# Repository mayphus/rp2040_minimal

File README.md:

> **Archived after consolidation — 18 September 2026.** Maintenance and original Git history now live in [hardware-designs](https://github.com/mayphus/hardware-designs/tree/main/boards/rp2040_minimal). This repository is retained as a historical reference; use the successor for new work.

---

# Minimal RP2040 Board

> **Status:** Hardware snapshot — preserved for reference and not actively maintained.

RP2040 minimal design with USB C

from RP2040 offical example.

[Minimal KiCAD](https://datasheets.raspberrypi.com/rp2040/Minimal-KiCAD.zip)
[Hardware design with rp2040](https://datasheets.raspberrypi.com/rp2040/hardware-design-with-rp2040.pdf)

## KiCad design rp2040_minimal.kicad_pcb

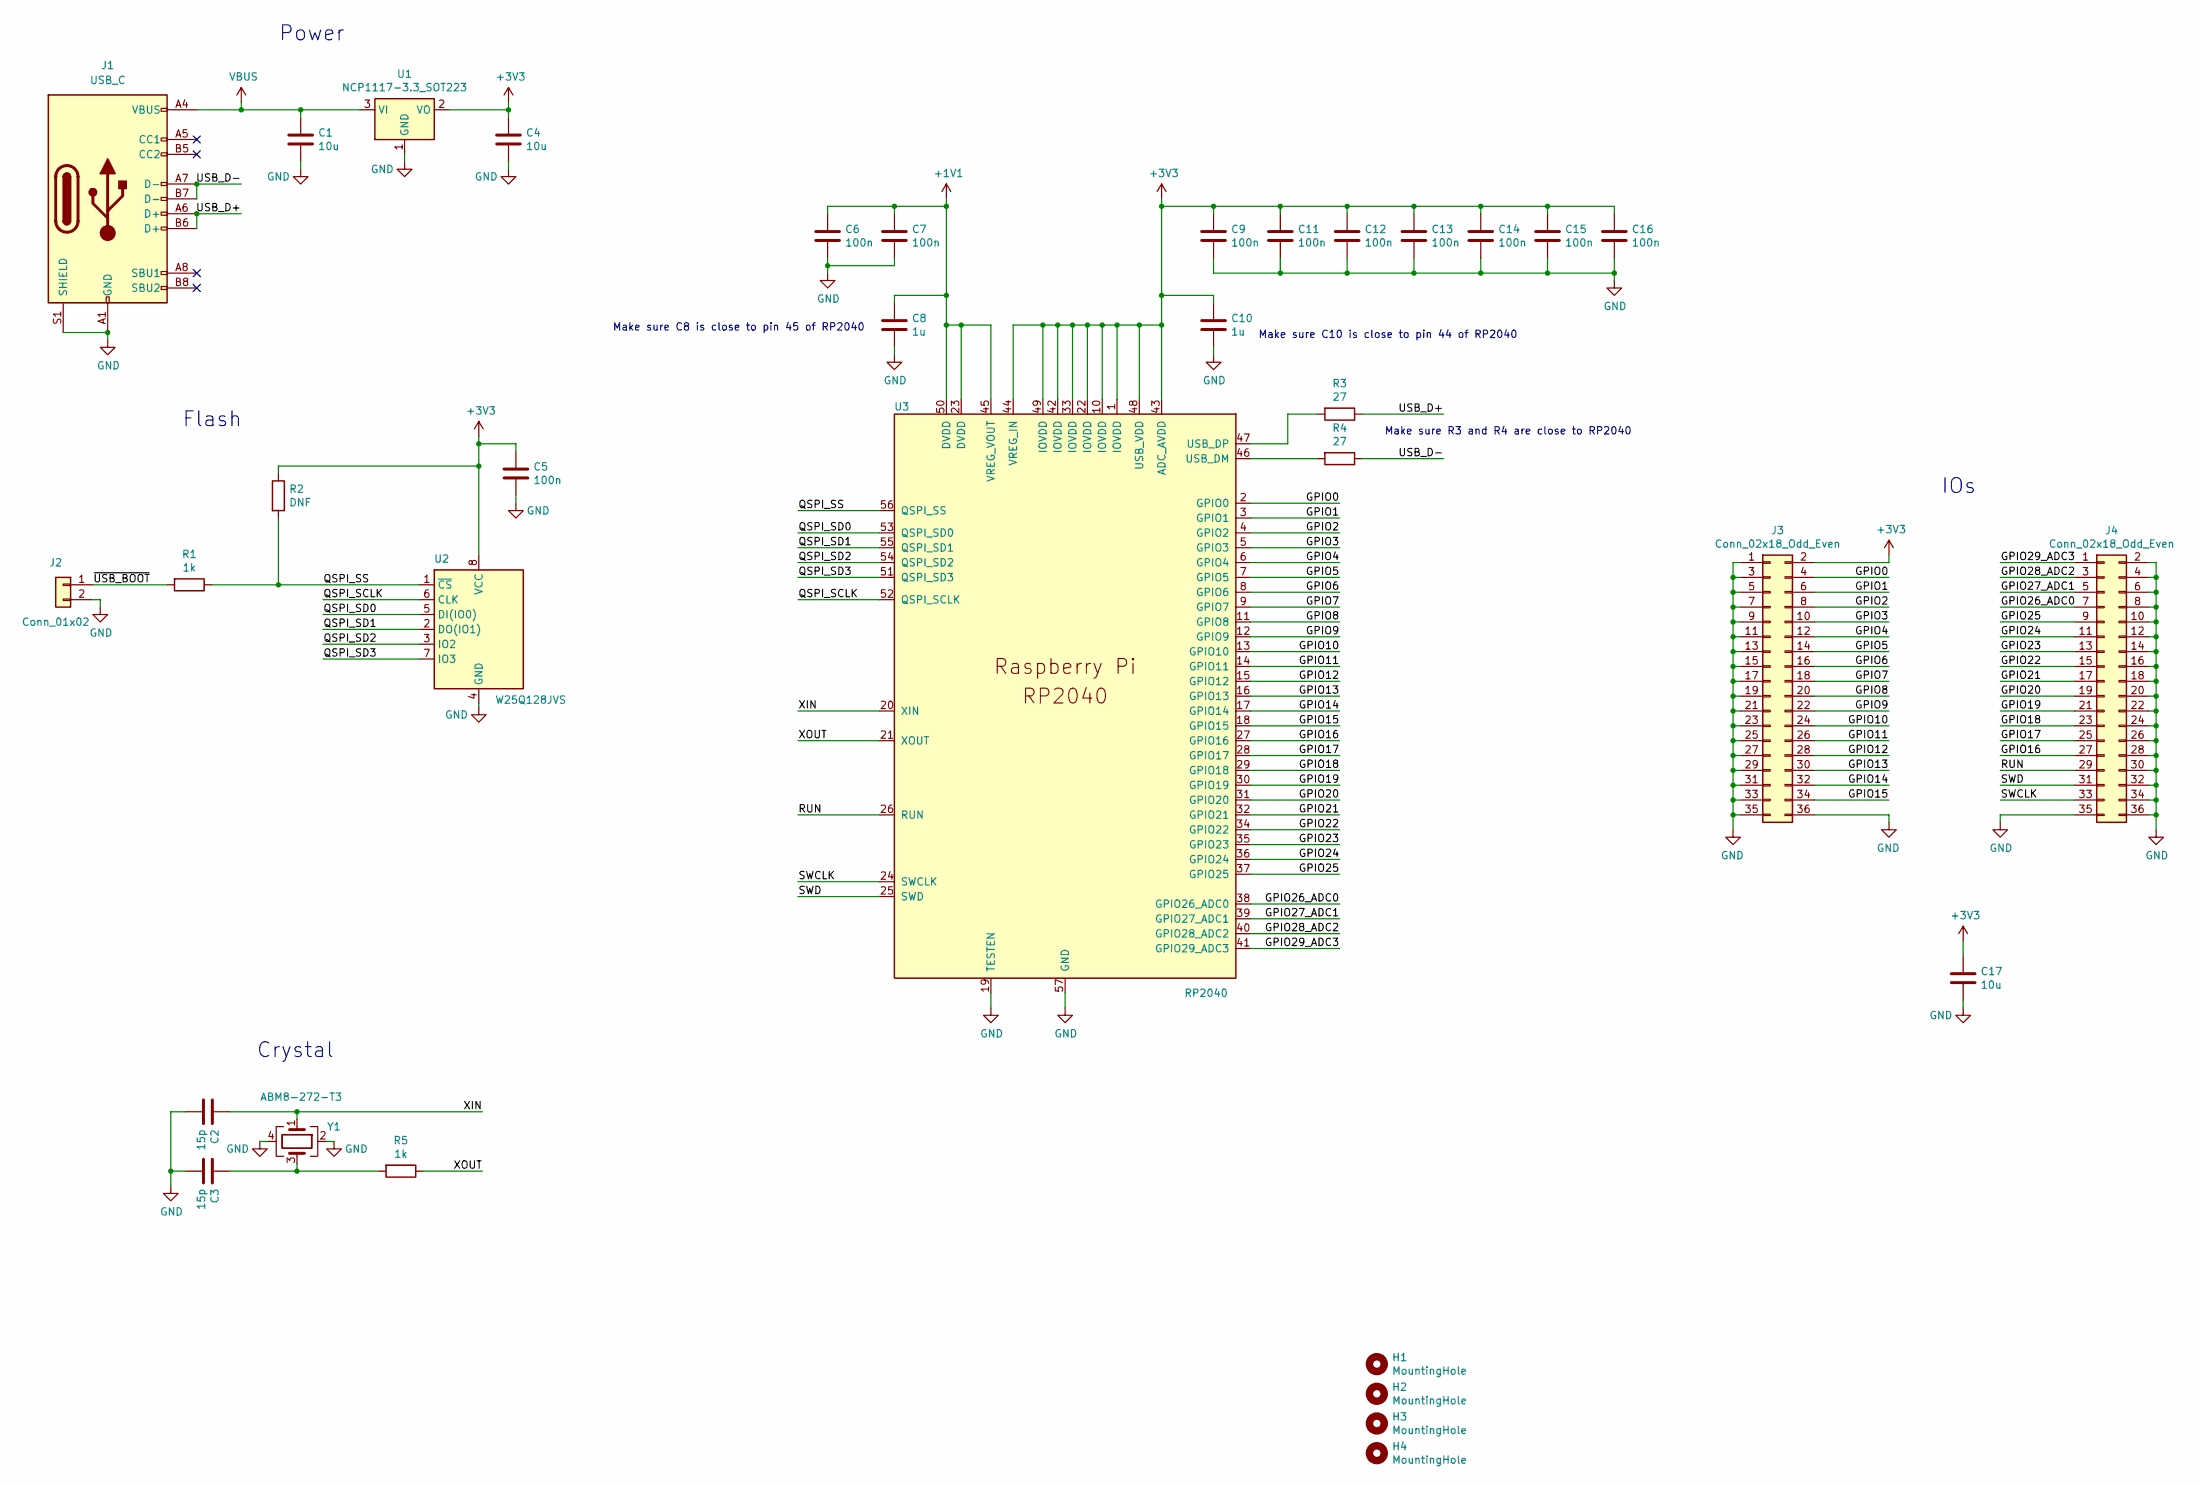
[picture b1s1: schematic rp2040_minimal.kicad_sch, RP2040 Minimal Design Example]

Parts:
C1, C4, C17: 10u; C_0805_2012Metric
C2, C3: 15p; C_0402_1005Metric
C5, C6, C7, C9, C11, C12, C13, C14, C15, C16: 100n; C_0402_1005Metric
C8, C10: 1u; C_0402_1005Metric
H1, H2, H3, H4: MountingHole; MountingHole_2.7mm_M2.5
J1: USB_C; USB_C_Receptacle_GCT_USB4105-xx-A_16P_TopMnt_Horizontal
J2: Conn_01x02; PinHeader_1x02_P2.54mm_Vertical
J3, J4: Conn_02x18_Odd_Even; PinHeader_2x18_P2.54mm_Vertical
R1, R5: 1k; R_0402_1005Metric
R2: DNF; R_0402_1005Metric
R3, R4: 27; R_0402_1005Metric
U1: NCP1117-3.3_SOT223; SOT-223-3_TabPin2
U2: W25Q128JVS; SOIC-8_5.23x5.23mm_P1.27mm
U3: RP2040; RP2040-QFN-56
Y1: ABM8-272-T3; Crystal_SMD_3225-4Pin_3.2x2.5mm

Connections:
+1V1: C6.1, C7.1, C8.1, U3.23 (DVDD), U3.45 (VREG_VOUT), U3.50 (DVDD)
+3V3: C4.1, C5.1, C9.1, C10.1, C11.1, C12.1, C13.1, C14.1, C15.1, C16.1, C17.1, J3.2, R2.1, U1.2 (VO), U2.8 (VCC), U3.1 (IOVDD), U3.10 (IOVDD), U3.22 (IOVDD), U3.33 (IOVDD), U3.42 (IOVDD), U3.43 (ADC_AVDD), U3.44 (VREG_IN), U3.48 (USB_VDD), U3.49 (IOVDD)
/GPIO0: J3.4, U3.2 (GPIO0)
/GPIO1: J3.6, U3.3 (GPIO1)
/GPIO2: J3.8, U3.4 (GPIO2)
/GPIO3: J3.10, U3.5 (GPIO3)
/GPIO4: J3.12, U3.6 (GPIO4)
/GPIO5: J3.14, U3.7 (GPIO5)
/GPIO6: J3.16, U3.8 (GPIO6)
/GPIO7: J3.18, U3.9 (GPIO7)
/GPIO8: J3.20, U3.11 (GPIO8)
/GPIO9: J3.22, U3.12 (GPIO9)
/GPIO10: J3.24, U3.13 (GPIO10)
/GPIO11: J3.26, U3.14 (GPIO11)
/GPIO12: J3.28, U3.15 (GPIO12)
/GPIO13: J3.30, U3.16 (GPIO13)
/GPIO14: J3.32, U3.17 (GPIO14)
/GPIO15: J3.34, U3.18 (GPIO15)
/GPIO16: J4.27, U3.27 (GPIO16)
/GPIO17: J4.25, U3.28 (GPIO17)
/GPIO18: J4.23, U3.29 (GPIO18)
/GPIO19: J4.21, U3.30 (GPIO19)
/GPIO20: J4.19, U3.31 (GPIO20)
/GPIO21: J4.17, U3.32 (GPIO21)
/GPIO22: J4.15, U3.34 (GPIO22)
/GPIO23: J4.13, U3.35 (GPIO23)
/GPIO24: J4.11, U3.36 (GPIO24)
/GPIO25: J4.9, U3.37 (GPIO25)
/GPIO26_ADC0: J4.7, U3.38 (GPIO26_ADC0)
/GPIO27_ADC1: J4.5, U3.39 (GPIO27_ADC1)
/GPIO28_ADC2: J4.3, U3.40 (GPIO28_ADC2)
/GPIO29_ADC3: J4.1, U3.41 (GPIO29_ADC3)
/QSPI_SCLK: U2.6 (CLK), U3.52 (QSPI_SCLK)
/QSPI_SD0: U2.5 (DI(IO0)), U3.53 (QSPI_SD0)
/QSPI_SD1: U2.2 (DO(IO1)), U3.55 (QSPI_SD1)
/QSPI_SD2: U2.3 (IO2), U3.54 (QSPI_SD2)
/QSPI_SD3: U2.7 (IO3), U3.51 (QSPI_SD3)
/QSPI_SS: R1.1, R2.2, U2.1 (~CS), U3.56 (QSPI_SS)
/RUN: J4.29, U3.26 (RUN)
/SWCLK: J4.33, U3.24 (SWCLK)
/SWD: J4.31, U3.25 (SWD)
/USB_D+: J1.A6 (D+), J1.B6 (D+), R3.1
/USB_D-: J1.A7 (D-), J1.B7 (D-), R4.1
/XIN: C2.1, U3.20 (XIN), Y1.1
/XOUT: R5.1, U3.21 (XOUT)
/~USB_BOOT: J2.1, R1.2
GND: C1.2, C2.2, C3.2, C4.2, C5.2, C6.2, C7.2, C8.2, C9.2, C10.2, C11.2, C12.2, C13.2, C14.2, C15.2, C16.2, C17.2, J1.A1 (GND), J1.A12 (GND), J1.B1 (GND), J1.B12 (GND), J1.S1 (SHIELD), J2.2, J3.1, J3.3, J3.5, J3.7, J3.9, J3.11, J3.13, J3.15, J3.17, J3.19, J3.21, J3.23, J3.25, J3.27, J3.29, J3.31, J3.33, J3.35, J3.36, J4.2, J4.4, J4.6, J4.8, J4.10, J4.12, J4.14, J4.16, J4.18, J4.20, J4.22, J4.24, J4.26, J4.28, J4.30, J4.32, J4.34, J4.35, J4.36, U1.1 (GND), U2.4 (GND), U3.19 (TESTEN), U3.57 (GND), Y1.2, Y1.4
unnamed: C3.1, R5.2, Y1.3
unnamed: R4.2, U3.46 (USB_DM)
unnamed: R3.2, U3.47 (USB_DP)
VBUS: C1.1, J1.A4 (VBUS), J1.A9 (VBUS), J1.B4 (VBUS), J1.B9 (VBUS), U1.3 (VI)

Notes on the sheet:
IOs
Power
Crystal
Make sure C8 is close to pin 45 of RP2040
Make sure C10 is close to pin 44 of RP2040
Make sure R3 and R4 are close to RP2040
Flash

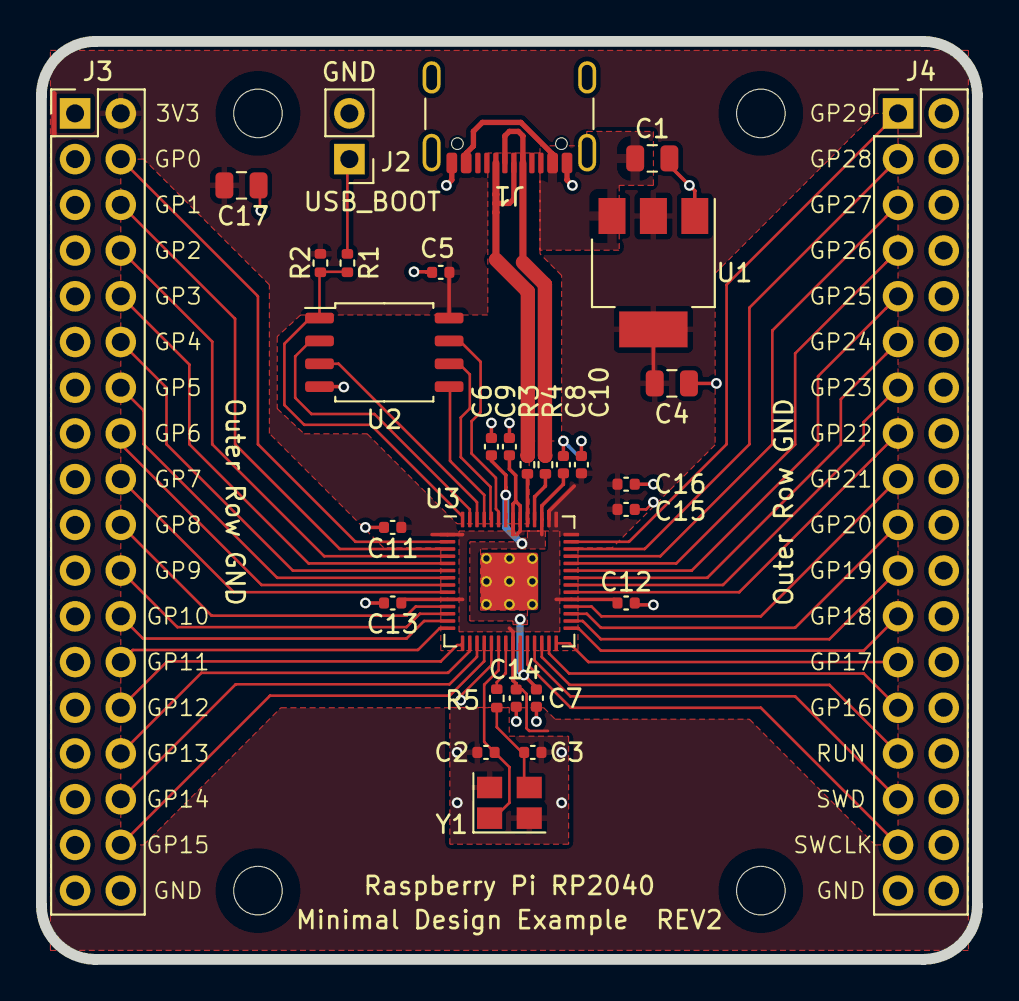
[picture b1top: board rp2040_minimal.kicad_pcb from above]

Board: 2 copper layers, 52.0 x 51.0 mm, 34 parts (0 on the bottom side), 51 nets.

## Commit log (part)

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2025-02-15 Initial
2025-02-15 add README.md
